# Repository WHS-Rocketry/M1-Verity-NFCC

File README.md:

## Current PCB validation

Open `NFCC.kicad_pro` in KiCad to load the project rules and bundled footprint library. The PCB includes the JLCPCB rule fixes and standard 2.54 mm GND / 5 V / PWM header spacing. See [change details](JLCPCB_FIXES.md).

Latest DRC: **0 violations, 0 unconnected items, 0 schematic parity issues**. Reports and a preview are in `checks/`. This is a prototype review design; a clean DRC does not establish production readiness. Power/load validation, final stackup and electrical/assembly review, and physical prototype testing remain necessary.

### Adjacent external connectors

The I²C and telemetry PicoBlade connectors are adjacent on the left edge, facing outward, with 12.2 mm between their centres. Their pin assignments are unchanged. The nearby battery-sense parts and I²C pullups were repositioned and the affected connections rerouted. The PWM headers retain 2.54 mm row spacing.

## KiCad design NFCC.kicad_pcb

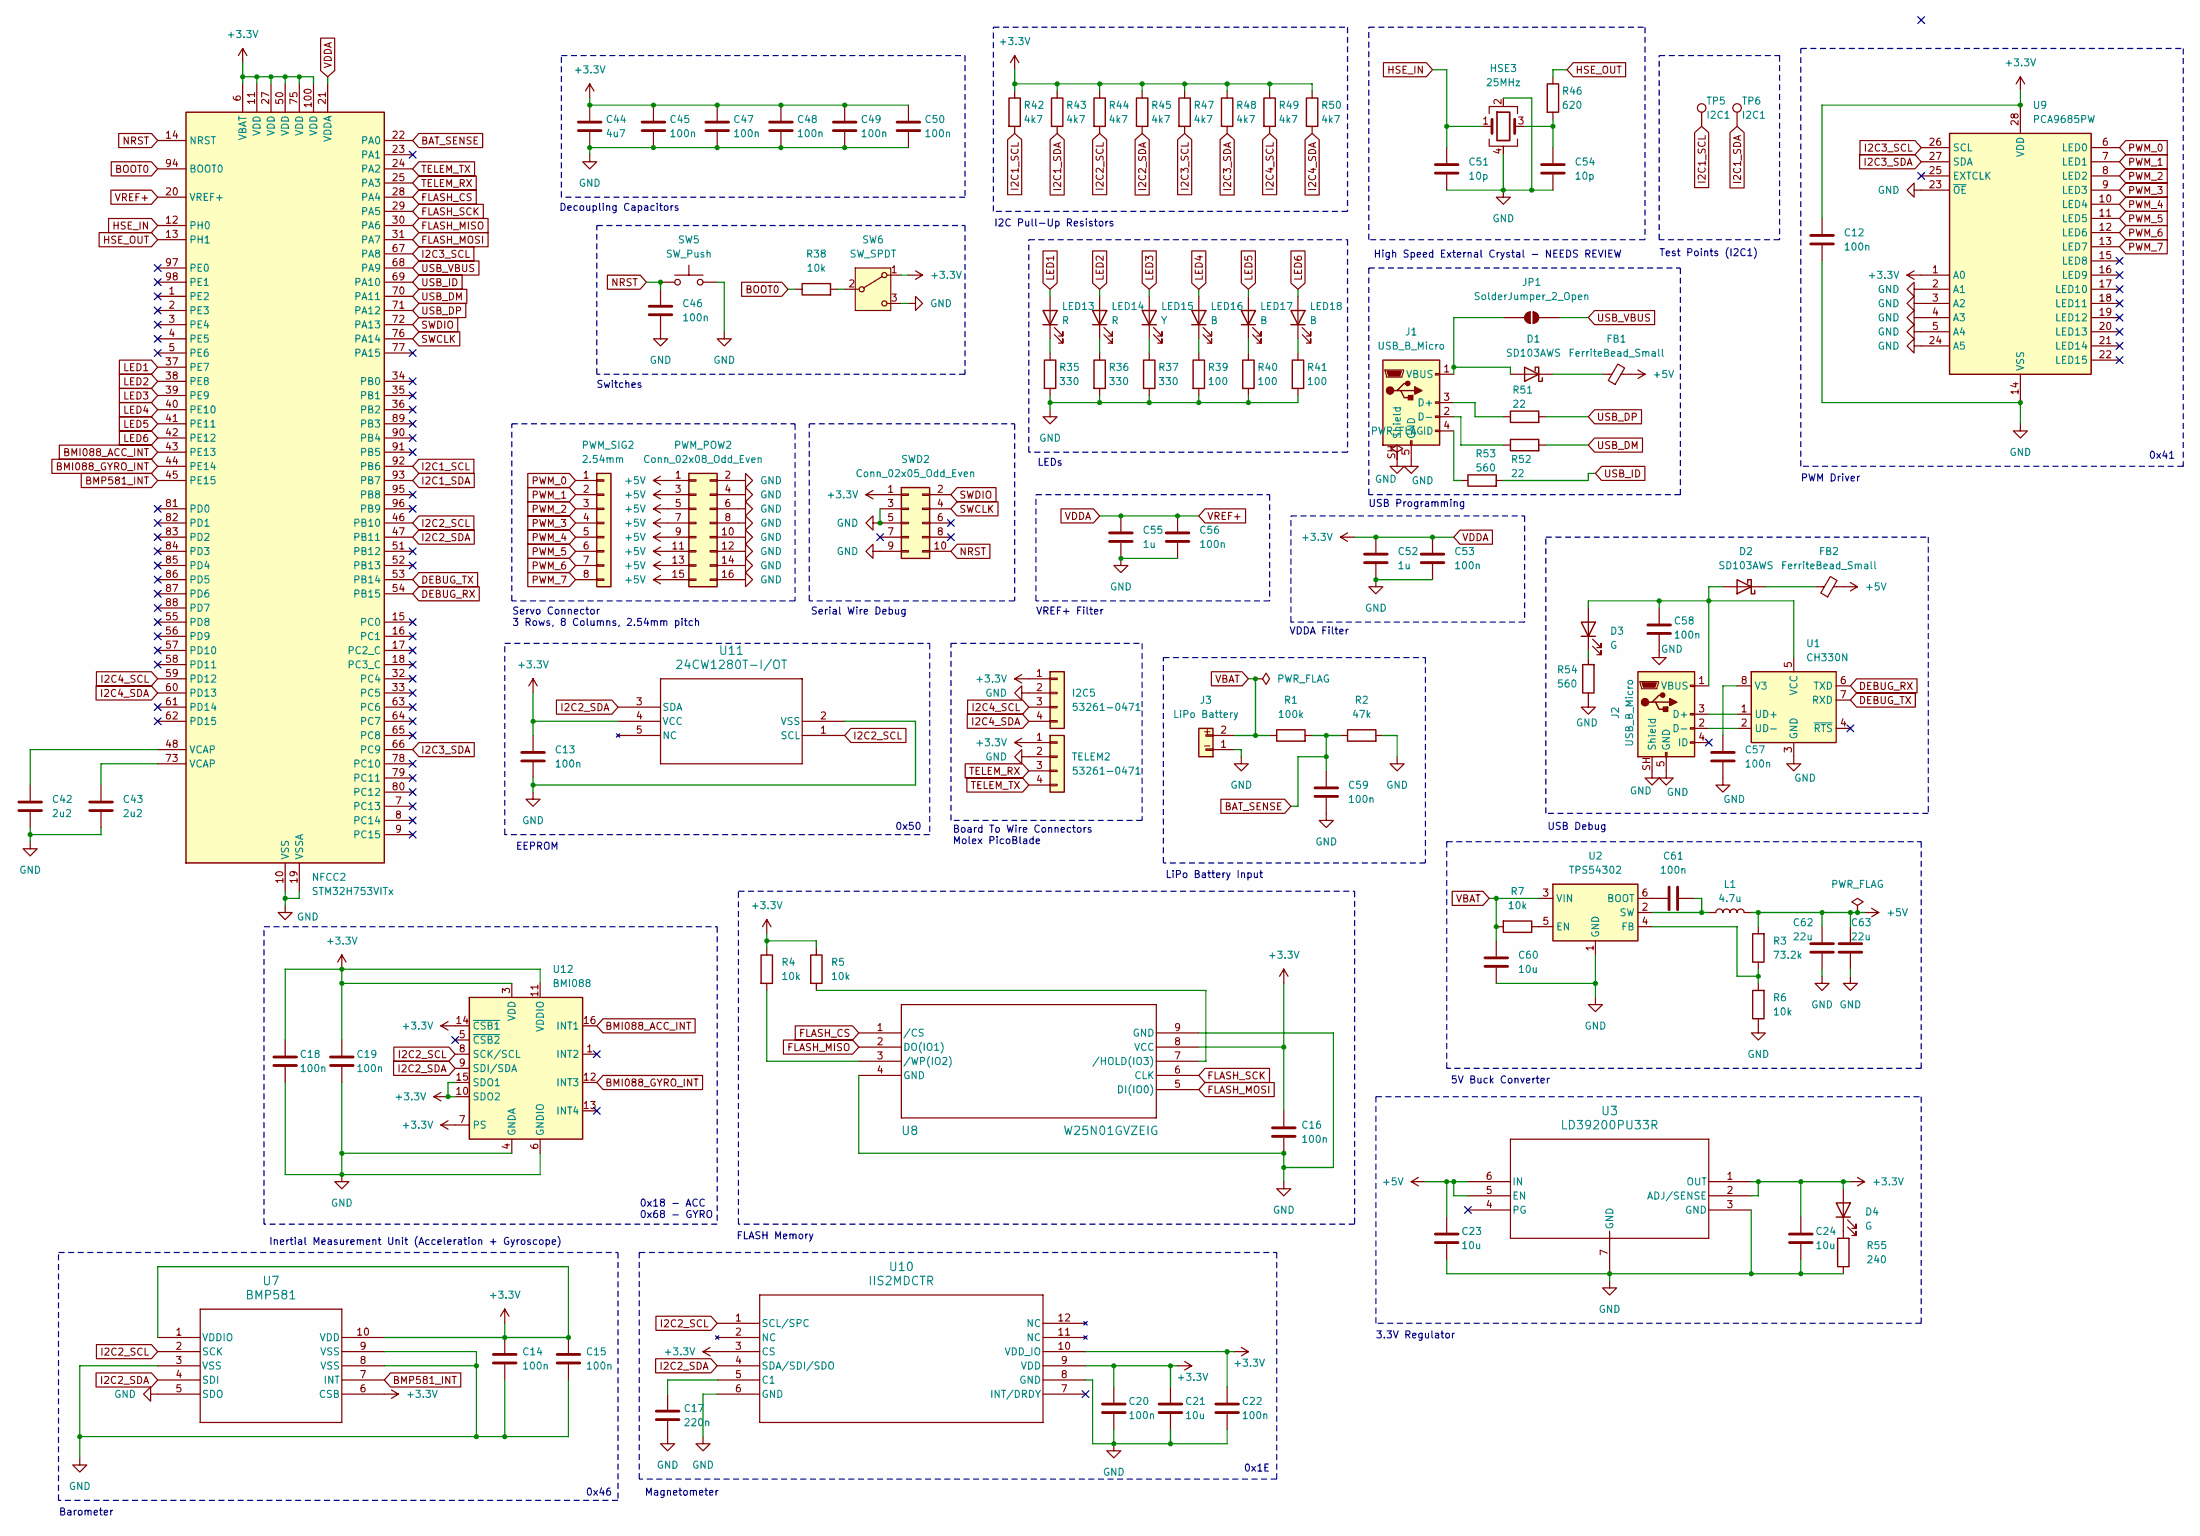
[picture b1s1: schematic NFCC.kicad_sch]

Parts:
C12: 100n; C_0603_1608Metric__C12
C13: 100n; C_0603_1608Metric__C13
C14: 100n; C_0603_1608Metric__C14
C15: 100n; C_0603_1608Metric__C15
C16: 100n; C_0603_1608Metric__C16
C17: 220n; C_0603_1608Metric__C17
C18: 100n; C_0603_1608Metric__C18
C19: 100n; C_0603_1608Metric__C19
C20: 100n; C_0603_1608Metric__C20
C21: 10u; C_0805_2012Metric__C21
C22: 100n; C_0603_1608Metric__C22
C23: 10u; C_0805_2012Metric__C23
C24: 10u; C_0805_2012Metric__C24
C42: 2u2; C_0603_1608Metric__C42
C43: 2u2; C_0603_1608Metric__C43
C44: 4u7; C_0603_1608Metric__C44
C45: 100n; C_0603_1608Metric__C45
C46: 100n; C_0603_1608Metric__C46
C47: 100n; C_0603_1608Metric__C47
C48: 100n; C_0603_1608Metric__C48
C49: 100n; C_0603_1608Metric__C49
C50: 100n; C_0603_1608Metric__C50
C51: 10p; C_0603_1608Metric__C51
C52: 1u; C_0603_1608Metric__C52
C53: 100n; C_0603_1608Metric__C53
C54: 10p; C_0603_1608Metric__C54
C55: 1u; C_0603_1608Metric__C55
C56: 100n; C_0603_1608Metric__C56
C57: 100n; C_0603_1608Metric__C57
C58: 100n; C_0603_1608Metric__C58
C59: 100n; C_0603_1608Metric__C59
C60: 10u; C_0805_2012Metric__C60
C61: 100n; C_0603_1608Metric__C61
C62: 22u; C_0805_2012Metric__C62
C63: 22u; C_0805_2012Metric__C63
D1: SD103AWS; D_SOD-323__D1
D2: SD103AWS; D_SOD-323__D2
D3: G; LED_0603_1608Metric__D3
D4: G; LED_0603_1608Metric__D4
FB1: FerriteBead_Small; L_0805_2012Metric__FB1
FB2: FerriteBead_Small; L_0805_2012Metric__FB2
HSE3: 25MHz; Crystal_SMD_3225-4Pin_3.2x2.5mm__HSE3
I2C5: 53261-0471; Molex_PicoBlade_53261-0471_1x04-1MP_P1.25mm_Horizontal__I2C5
J1: USB_B_Micro; USB_Micro-B_Molex_47346-0001__J1
J2: USB_B_Micro; USB_Micro-B_Molex_47346-0001__J2
J3: LiPo Battery; AMASS_XT60-M_1x02_P7.20mm_Vertical__J3
JP1: SolderJumper_2_Open; SolderJumper-2_P1.3mm_Open_RoundedPad1.0x1.5mm__JP1
L1: 4.7u; L_Bourns_SRN6045TA__L1
LED13: R; LED_0603_1608Metric__LED13
LED14: R; LED_0603_1608Metric__LED14
LED15: Y; LED_0603_1608Metric__LED15
LED16: B; LED_0603_1608Metric__LED16
LED17: B; LED_0603_1608Metric__LED17
LED18: B; LED_0603_1608Metric__LED18
NFCC2: STM32H753VITx; LQFP-100_14x14mm_P0.5mm__NFCC2
PWM_POW2: Conn_02x08_Odd_Even; PinHeader_2x08_P2.54mm_Vertical__PWM_POW2
PWM_SIG2: 2.54mm; PinHeader_1x08_P2.54mm_Vertical__PWM_SIG2
R1: 100k; R_0603_1608Metric__R1
R2: 47k; R_0603_1608Metric__R2
R3: 73.2k; R_0603_1608Metric__R3
R4: 10k; R_0603_1608Metric__R4
R5: 10k; R_0603_1608Metric__R5
R6: 10k; R_0603_1608Metric__R6
R7: 10k; R_0603_1608Metric__R7
R35: 330; R_0603_1608Metric__R35
R36: 330; R_0603_1608Metric__R36
R37: 330; R_0603_1608Metric__R37
R38: 10k; R_0603_1608Metric__R38
R39: 100; R_0603_1608Metric__R39
R40: 100; R_0603_1608Metric__R40
R41: 100; R_0603_1608Metric__R41
R42: 4k7; R_0603_1608Metric__R42
R43: 4k7; R_0603_1608Metric__R43
R44: 4k7; R_0603_1608Metric__R44
R45: 4k7; R_0603_1608Metric__R45
R46: 620; R_0603_1608Metric__R46
R47: 4k7; R_0603_1608Metric__R47
R48: 4k7; R_0603_1608Metric__R48
R49: 4k7; R_0603_1608Metric__R49
R50: 4k7; R_0603_1608Metric__R50
R51: 22; R_0603_1608Metric__R51
R52: 22; R_0603_1608Metric__R52
R53: 560; R_0603_1608Metric__R53
R54: 560; R_0603_1608Metric__R54
R55: 240; R_0603_1608Metric__R55
SW5: SW_Push; SW_SPST_SKQG_WithoutStem__SW5
SW6: SW_SPDT; SW_SPDT_PCM12__SW6
SWD2: Conn_02x05_Odd_Even; PinHeader_2x05_P1.27mm_Vertical__SWD2
TELEM2: 53261-0471; Molex_PicoBlade_53261-0471_1x04-1MP_P1.25mm_Horizontal__TEL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
TP5: I2C1; TestPoint_Pad_D1.5mm__TP5
TP6: I2C1; TestPoint_Pad_D1.5mm__TP6
U1: CH330N; SOIC-8_3.9x4.9mm_P1.27mm__U1
U2: TPS54302; SOT-23-6__U2
U3: LD39200PU33R; SON_DFN6_3X3_STM__U3
U7: BMP581; QFN10_BMP581_BOS__U7
U8: W25N01GVZEIG; WSON-8_8X6_WIN__U8
U9: PCA9685PW; TSSOP-28_4.4x9.7mm_P0.65mm__U9
U10: IIS2MDCTR; LGA-12_2X2X0P7_STM__U10
U11: 24CW1280T-I/OT; SOT-23-5_2P9X1P6_MCH__U11
U12: BMI088; Bosch_LGA-16_4.5x3mm_P0.5mm_LayoutBorder7x1y_ClockwisePinNu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

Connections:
+5V: C23.1, C62.1, C63.1, FB1.2, FB2.2, L1.2, PWM_POW2.1, PWM_POW2.3, PWM_POW2.5, PWM_POW2.7, PWM_POW2.9, PWM_POW2.11, PWM_POW2.13, PWM_POW2.15, R3.2, U3.5 (EN), U3.6 (IN)
BAT_SENSE: C59.1, NFCC2.22 (PA0), R1.2, R2.1
BMI088_ACC_INT: NFCC2.43 (PE13), U12.16 (INT1)
BMI088_GYRO_INT: NFCC2.44 (PE14), U12.12 (INT3)
BMP581_INT: NFCC2.45 (PE15), U7.7 (INT)
BOOT0: NFCC2.94 (BOOT0), R38.1
DEBUG_RX: NFCC2.54 (PB15), U1.6 (TXD)
DEBUG_TX: NFCC2.53 (PB14), U1.7 (RXD)
FLASH_CS: NFCC2.28 (PA4), U8.1 (/CS)
FLASH_MISO: NFCC2.30 (PA6), U8.2 (DO(IO1))
FLASH_MOSI: NFCC2.31 (PA7), U8.5 (DI(IO0))
FLASH_SCK: NFCC2.29 (PA5), U8.6 (CLK)
GND: C12.2, C13.2, C14.2, C15.2, C16.2, C17.2, C18.2, C19.2, C20.2, C21.2, C22.2, C23.2, C24.2, C42.2, C43.2, C44.2, C45.2, C46.2, C47.2, C48.2, C49.2, C50.2, C51.2, C52.2, C53.2, C54.2, C55.2, C56.2, C57.2, C58.2, C59.2, C60.2, C62.2, C63.2, HSE3.2, HSE3.4, I2C5.2, I2C5.MP (Mount_GND), J1.5 (GND), J1.SH (Shield), J2.5 (GND), J2.SH (Shield), J3.1, NFCC2.10 (VSS), NFCC2.19 (VSSA), NFCC2.26 (VSS), NFCC2.49 (VSS), NFCC2.74 (VSS), NFCC2.99 (VSS), PWM_POW2.2, PWM_POW2.4, PWM_POW2.6, PWM_POW2.8, PWM_POW2.10, PWM_POW2.12, PWM_POW2.14, PWM_POW2.16, R2.2, R6.1, R35.2, R36.2, R37.2, R39.2, R40.2, R41.2, R54.1, R55.1, SW5.2, SW6.3 (C), SWD2.3, SWD2.5, SWD2.9, TELEM2.2, TELEM2.MP (Mount_GND), U1.3 (GND), U2.1 (GND), U3.3 (GND), U3.7 (GND), U7.3 (VSS), U7.5 (SDO), U7.8 (VSS), U7.9 (VSS), U8.4 (GND), U8.9 (GND), U9.2 (A1), U9.3 (A2), U9.4 (A3), U9.5 (A4), U9.14 (VSS), U9.23 (~OE), U9.24 (A5), U10.6 (GND), U10.8 (GND), U11.2 (VSS), U12.2 (GNDA), U12.4 (GNDA), U12.6 (GNDIO)
HSE_IN: C51.1, HSE3.1, NFCC2.12 (PH0)
HSE_OUT: NFCC2.13 (PH1), R46.1
I2C1_SCL: NFCC2.92 (PB6), R42.2, TP5.1
I2C1_SDA: NFCC2.93 (PB7), R43.2, TP6.1
I2C2_SCL: NFCC2.46 (PB10), R44.2, U7.2 (SCK), U10.1 (SCL/SPC), U11.1 (SCL), U12.8 (SCK/SCL)
I2C2_SDA: NFCC2.47 (PB11), R45.2, U7.4 (SDI), U10.4 (SDA/SDI/SDO), U11.3 (SDA), U12.9 (SDI/SDA)
I2C3_SCL: NFCC2.67 (PA8), R47.2, U9.26 (SCL)
I2C3_SDA: NFCC2.66 (PC9), R48.2, U9.27 (SDA)
I2C4_SCL: I2C5.3, NFCC2.59 (PD12), R49.2
I2C4_SDA: I2C5.4, NFCC2.60 (PD13), R50.2
LED1: LED13.2 (A), NFCC2.37 (PE7)
LED2: LED14.2 (A), NFCC2.38 (PE8)
LED3: LED15.2 (A), NFCC2.39 (PE9)
LED4: LED16.2 (A), NFCC2.40 (PE10)
LED5: LED17.2 (A), NFCC2.41 (PE11)
LED6: LED18.2 (A), NFCC2.42 (PE12)
NRST: C46.1, NFCC2.14 (NRST), SW5.1, SWD2.10
unnamed: C42.1, NFCC2.48 (VCAP)
unnamed: C43.1, NFCC2.73 (VCAP)
unnamed: C54.1, HSE3.3, R46.2
unnamed: D1.2 (A), J1.1 (VBUS), JP1.1 (A)
unnamed: D1.1 (K), FB1.1
unnamed: C58.1, D2.2 (A), D3.2 (A), J2.1 (VBUS), U1.5 (VCC)
unnamed: D2.1 (K), FB2.1
unnamed: D3.1 (K), R54.2
unnamed: D4.1 (K), R55.2
unnamed: J1.3 (D+), R51.1
unnamed: J1.2 (D-), R52.1
unnamed: J1.4 (ID), R53.1
unnamed: J2.3 (D+), U1.1 (UD+)
unnamed: J2.2 (D-), U1.2 (UD-)
unnamed: LED13.1 (K), R35.1
unnamed: LED14.1 (K), R36.1
unnamed: LED15.1 (K), R37.1
unnamed: LED16.1 (K), R39.1
unnamed: LED17.1 (K), R40.1
unnamed: LED18.1 (K), R41.1
unnamed: R38.2, SW6.2 (B)
unnamed: C57.1, U1.8 (V3)
unnamed: C61.1, U2.6 (BOOT)
unnamed: R7.1, U2.5 (EN)
unnamed: R3.1, R6.2, U2.4 (FB)
unnamed: C61.2, L1.1, U2.2 (SW)
unnamed: R5.2, U8.7 (/HOLD(IO3))
unnamed: R4.2, U8.3 (/WP(IO2))
unnamed: C17.1, U10.5 (C1)
PWM_0: PWM_SIG2.1, U9.6 (LED0)
PWM_1: PWM_SIG2.2, U9.7 (LED1)
PWM_2: PWM_SIG2.3, U9.8 (LED2)
PWM_3: PWM_SIG2.4, U9.9 (LED3)
PWM_4: PWM_SIG2.5, U9.10 (LED4)
PWM_5: PWM_SIG2.6, U9.11 (LED5)
PWM_6: PWM_SIG2.7, U9.12 (LED6)
PWM_7: PWM_SIG2.8, U9.13 (LED7)
SWCLK: NFCC2.76 (PA14), SWD2.4
SWDIO: NFCC2.72 (PA13), SWD2.2
TELEM_RX: NFCC2.25 (PA3), TELEM2.3
TELEM_TX: NFCC2.24 (PA2), TELEM2.4
USB_DM: NFCC2.70 (PA11), R52.2
USB_DP: NFCC2.71 (PA12), R51.2
USB_ID: NFCC2.69 (PA10), R53.2
USB_VBUS: JP1.2 (B), NFCC2.68 (PA9)
VBAT: C60.1, J3.2, R1.1, R7.2, U2.3 (VIN)
VDDA: C12.1, C13.1, C14.1, C15.1, C16.1, C18.1, C19.1, C20.1, C21.1, C22.1, C24.1, C44.1, C45.1, C47.1, C48.1, C49.1, C50.1, C52.1, C53.1, C55.1, C56.1, D4.2 (A), I2C5.1, NFCC2.6 (VBAT), NFCC2.11 (VDD), NFCC2.20 (VREF+), NFCC2.21 (VDDA), NFCC2.27 (VDD), NFCC2.50 (VDD), NFCC2.75 (VDD), NFCC2.100 (VDD), R4.1, R5.1, R42.1, R43.1, R44.1, R45.1, R47.1, R48.1, R49.1, R50.1, SW6.1 (A), SWD2.1, TELEM2.1, U3.1 (OUT), U3.2 (ADJ/SENSE), U7.1 (VDDIO), U7.6 (CSB), U7.10 (VDD), U8.8 (VCC), U9.1 (A0), U9.28 (VDD), U10.3 (CS), U10.9 (VDD), U10.10 (VDD_IO), U11.4 (VCC), U12.3 (VDD), U12.7 (PS), U12.10 (SDO2), U12.11 (VDDIO), U12.14 (~CSB1), U12.15 (SDO1)

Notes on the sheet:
LiPo Battery Input
PWM Driver
Board To Wire Connectors Molex PicoBlade
LEDs
Servo Connector 3 Rows, 8 Columns, 2.54mm pitch
FLASH Memory
I2C Pull-Up Resistors
0x1E
VDDA Filter
Decoupling Capacitors
Switches
0x41
0x46
0x18 - ACC 0x68 - GYRO
VREF+ Filter
5V Buck Converter
Magnetometer
Test Points (I2C1)
3.3V Regulator
Serial Wire Debug
0x50
USB Debug
USB Programming
Barometer
Inertial Measurement Unit (Acceleration + Gyroscope)
High Speed External Crystal - NEEDS REVIEW
EEPROM

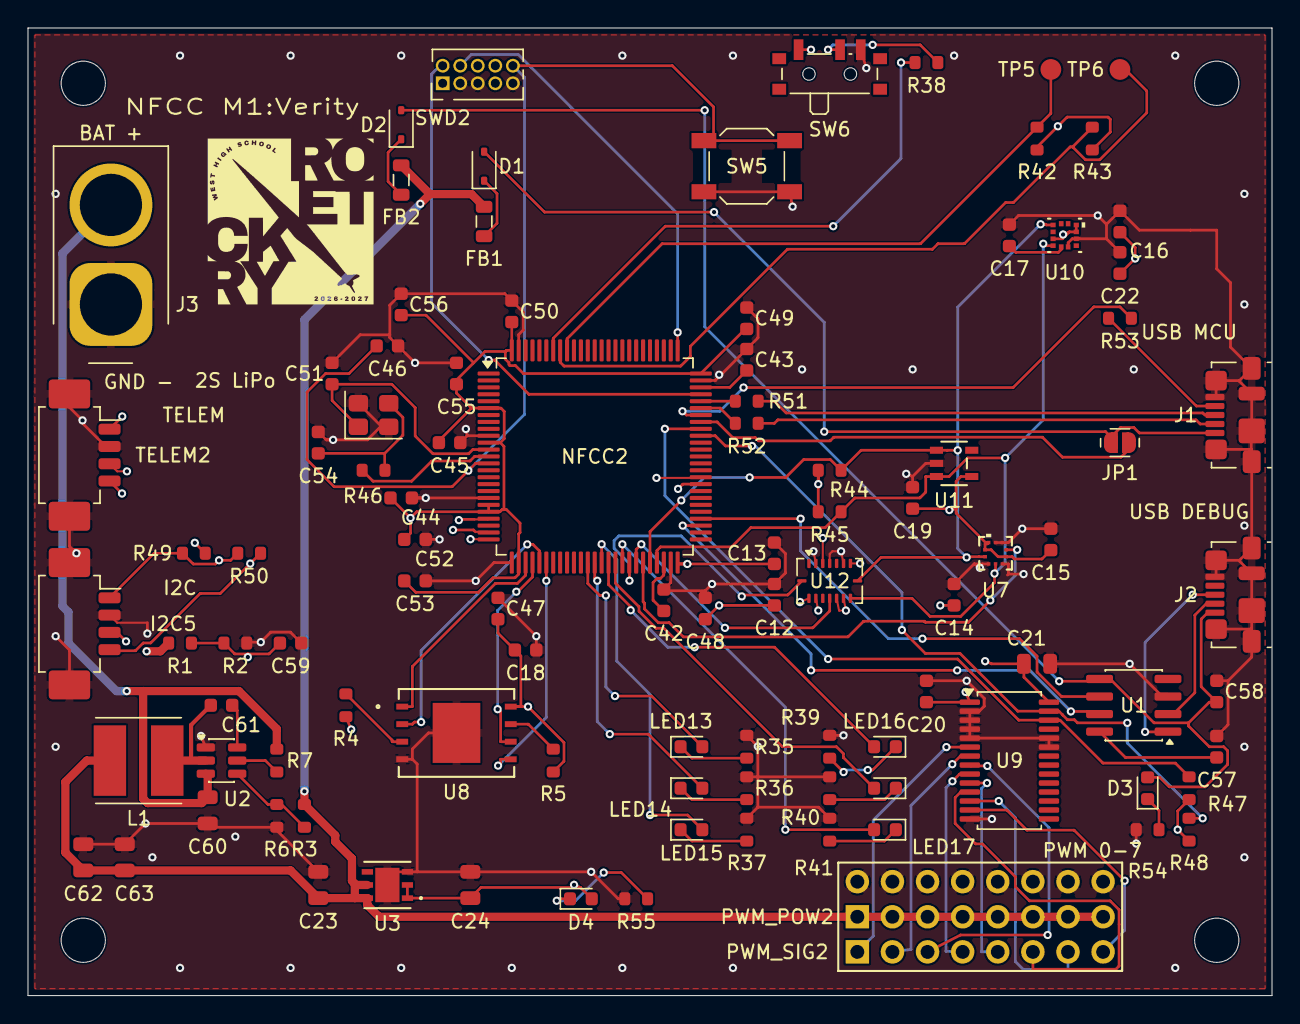
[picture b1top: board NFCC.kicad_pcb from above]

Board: 4 copper layers, 90.0 x 70.0 mm, 104 parts (0 on the bottom side), 77 nets.

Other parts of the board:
H1, H2, H3, H4: M3; MountingHole_3.2mm_M3

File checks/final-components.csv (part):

reference,value,footprint,x_mm,y_mm,rotation_deg
C12,100n,<pcbnew.LIB_ID; proxy of <Swig Object of type 'LIB_ID *' at 0x104eae8f0> >,114.0,101.0,90.0
C13,100n,<pcbnew.LIB_ID; proxy of <Swig Object of type 'LIB_ID *' at 0x10539ddf0> >,114.0,98.0,90.0
C14,100n,<pcbnew.LIB_ID; proxy of <Swig Object of type 'LIB_ID *' at 0x1053ae130> >,127.0,101.0,90.0
C15,100n,<pcbnew.LIB_ID; proxy of <Swig Object of type 'LIB_ID *' at 0x1052aca30> >,134.0,97.0,90.0
C16,100n,<pcbnew.LIB_ID; proxy of <Swig Object of type 'LIB_ID *' at 0x1052ac870> >,139.0,74.0,90.0
C17,220n,<pcbnew.LIB_ID; proxy of <Swig Object of type 'LIB_ID *' at 0x1052acd30> >,131.0,75.0,90.0
C18,100n,<pcbnew.LIB_ID; proxy of <Swig Object of type 'LIB_ID *' at 0x1052acc30> >,96.0,105.0,0.0
C19,100n,<pcbnew.LIB_ID; proxy of <Swig Object of type 'LIB_ID *' at 0x1052aca30> >,124.0,94.0,90.0
C20,100n,<pcbnew.LIB_ID; proxy of <Swig Object of type 'LIB_ID *' at 0x1052ac870> >,125.0,108.0,90.0
C21,10u,<pcbnew.LIB_ID; proxy of <Swig Object of type 'LIB_ID *' at 0x1052acd30> >,133.0,106.0,0.0
C22,100n,<pcbnew.LIB_ID; proxy of <Swig Object of type 'LIB_ID *' at 0x1052acc30> >,139.0,77.0,90.0
C23,10u,<pcbnew.LIB_ID; proxy of <Swig Object of type 'LIB_ID *' at 0x1052ac5b0> >,81.0,122.0,90.0
C24,10u,<pcbnew.LIB_ID; proxy of <Swig Object of type 'LIB_ID *' at 0x1052ac870> >,92.0,122.0,90.0
C42,2u2,<pcbnew.LIB_ID; proxy of <Swig Object of type 'LIB_ID *' at 0x1052acd30> >,106.0,101.4,90.0
C43,2u2,<pcbnew.LIB_ID; proxy of <Swig Object of type 'LIB_ID *' at 0x1052acc30> >,112.0,84.0,90.0
C44,4u7,<pcbnew.LIB_ID; proxy of <Swig Object of type 'LIB_ID *' at 0x1052ac5b0> >,87.0,94.0,0.0
C45,100n,<pcbnew.LIB_ID; proxy of <Swig Object of type 'LIB_ID *' at 0x1052ac870> >,90.5,90.0,0.0
C46,100n,<pcbnew.LIB_ID; proxy of <Swig Object of type 'LIB_ID *' at 0x1052acd30> >,86.0,83.0,0.0
C47,100n,<pcbnew.LIB_ID; proxy of <Swig Object of type 'LIB_ID *' at 0x1052acc30> >,94.0,102.0,90.0
C48,100n,<pcbnew.LIB_ID; proxy of <Swig Object of type 'LIB_ID *' at 0x1052ac5b0> >,109.0,102.0,90.0
C49,100n,<pcbnew.LIB_ID; proxy of <Swig Object of type 'LIB_ID *' at 0x1052ac870> >,112.0,81.0,90.0
C50,100n,<pcbnew.LIB_ID; proxy of <Swig Object of type 'LIB_ID *' at 0x1052acd30> >,95.0,80.5,90.0
C51,10p,<pcbnew.LIB_ID; proxy of <Swig Object of type 'LIB_ID *' at 0x1052acc30> >,82.0,85.0,90.0
C52,1u,<pcbnew.LIB_ID; proxy of <Swig Object of type 'LIB_ID *' at 0x1052ac5b0> >,88.0,97.0,0.0
C53,100n,<pcbnew.LIB_ID; proxy of <Swig Object of type 'LIB_ID *' at 0x1052ac870> >,88.0,100.0,0.0
C54,10p,<pcbnew.LIB_ID; proxy of <Swig Object of type 'LIB_ID *' at 0x1052acd30> >,81.0,90.0,90.0
C55,1u,<pcbnew.LIB_ID; proxy of <Swig Object of type 'LIB_ID *' at 0x1052acc30> >,91.0,85.0,90.0
C56,100n,<pcbnew.LIB_ID; proxy of <Swig Object of type 'LIB_ID *' at 0x1052ac5b0> >,87.0,80.0,90.0
C57,100n,<pcbnew.LIB_ID; proxy of <Swig Object of type 'LIB_ID *' at 0x1052ac870> >,146.0,112.0,90.0
C58,100n,<pcbnew.LIB_ID; proxy of <Swig Object of type 'LIB_ID *' at 0x1052acd30> >,146.0,108.0,90.0
C59,100n,<pcbnew.LIB_ID; proxy of <Swig Object of type 'LIB_ID *' at 0x1052acc30> >,71.0,103.0,0.0
C60,10u,<pcbnew.LIB_ID; proxy of <Swig Object of type 'LIB_ID *' at 0x1052ac5b0> >,73.0,116.6,-90.0
C61,100n,<pcbnew.LIB_ID; proxy of <Swig Object of type 'LIB_ID *' at 0x1052ac870> >,74.0,109.0,180.0
C62,22u,<pcbnew.LIB_ID; proxy of <Swig Object of type 'LIB_ID *' at 0x1052acd30> >,64.0,120.0,90.0
C63,22u,<pcbnew.LIB_ID; proxy of <Swig Object of type 'LIB_ID *' at 0x1052acc30> >,67.0,120.0,90.0
D1,SD103AWS,<pcbnew.LIB_ID; proxy of <Swig Object of type 'LIB_ID *' at 0x1052ac5b0> >,93.0,70.0,90.0
D2,SD103AWS,<pcbnew.LIB_ID; proxy of <Swig Object of type 'LIB_ID *' at 0x1052ac870> >,87.0,67.0,90.0
D3,G,<pcbnew.LIB_ID; proxy of <Swig Object of type 'LIB_ID *' at 0x1052acd30> >,141.0,115.0,90.0
D4,G,<pcbnew.LIB_ID; proxy of <Swig Object of type 'LIB_ID *' at 0x1052acc30> >,100.0,123.0,0.0
FB1,FerriteBead_Small,<pcbnew.LIB_ID; proxy of <Swig Object of type 'LIB_ID *' at 0x1052ac5b0> >,93.0,74.0,90.0
FB2,FerriteBead_Small,<pcbnew.LIB_ID; proxy of <Swig Object of type 'LIB_ID *' at 0x1052ac270> >,87.0,71.0,90.0
G***,LOGO,<pcbnew.LIB_ID; proxy of <Swig Object of type 'LIB_ID *' at 0x1052acd30> >,79.0,74.0,0.0
H1,M3,<pcbnew.LIB_ID; proxy of <Swig Object of type 'LIB_ID *' at 0x1052acc30> >,64.0,64.0,0.0
H2,M3,<pcbnew.LIB_ID; proxy of <Swig Object of type 'LIB_ID *' at 0x1052ac5b0> >,146.0,64.0,0.0
H3,M3,<pcbnew.LIB_ID; proxy of <Swig Object of type 'LIB_ID *' at 0x1052aceb0> >,146.0,126.0,0.0
H4,M3,<pcbnew.LIB_ID; proxy of <Swig Object of type 'LIB_ID *' at 0x1052acd30> >,64.0,126.0,0.0
HSE3,25MHz,<pcbnew.LIB_ID; proxy of <Swig Object of type 'LIB_ID *' at 0x1052acc30> >,85.0,88.0,0.0
I2C5,53261-0471,<pcbnew.LIB_ID; proxy of <Swig Object of type 'LIB_ID *' at 0x1052ac5b0> >,146.5,74.0,90.0
J1,USB_B_Micro,<pcbnew.LIB_ID; proxy of <Swig Object of type 'LIB_ID *' at 0x1052aceb0> >,147.33,88.0,90.0
J2,USB_B_Micro,<pcbnew.LIB_ID; proxy of <Swig Object of type 'LIB_ID *' at 0x1052acd30> >,147.33,101.0,90.0
J3,LiPo Battery,<pcbnew.LIB_ID; proxy of <Swig Object of type 'LIB_ID *' at 0x1052acc30> >,66.0,80.0,90.0
JP1,SolderJumper_2_Open,<pcbnew.LIB_ID; proxy of <Swig Object of type 'LIB_ID *' at 0x1052ac5b0> >,139.0,90.0,0.0
L1,4.7u,<pcbnew.LIB_ID; proxy of <Swig Object of type 'LIB_ID *' at 0x1052aceb0> >,68.0,113.0,180.0
LED13,R,<pcbnew.LIB_ID; proxy of <Swig Object of type 'LIB_ID *' at 0x1052acd30> >,108.0,112.0,0.0
LED14,R,<pcbnew.LIB_ID; proxy of <Swig Object of type 'LIB_ID *' at 0x1052acef0> >,108.0,115.0,0.0
LED15,Y,<pcbnew.LIB_ID; proxy of <Swig Object of type 'LIB_ID *' at 0x1052ac430> >,108.0,118.0,0.0
LED16,B,<pcbnew.LIB_ID; proxy of <Swig Object of type 'LIB_ID *' at 0x1052acc30> >,122.0,112.0,180.0
LED17,B,<pcbnew.LIB_ID; proxy of <Swig Object of type 'LIB_ID *' at 0x1052acd30> >,122.0,115.0,180.0
LED18,B,<pcbnew.LIB_ID; proxy of <Swig Object of type 'LIB_ID *' at 0x1052acef0> >,122.0,118.0,180.0
NFCC2,STM32H753VITx,<pcbnew.LIB_ID; proxy of <Swig Object of type 'LIB_ID *' at 0x1052acd30> >,101.0,91.0,0.0
PWM_POW2,Conn_02x08_Odd_Even,<pcbnew.LIB_ID; proxy of <Swig Object of type 'LIB_ID *' at 0x1052acef0> >,120.0,124.3,90.0
PWM_SIG2,2.54mm,<pcbnew.LIB_ID; proxy of <Swig Object of type 'LIB_ID *' at 0x1052de0f0> >,120.0,128.0,90.0
R1,100k,<pcbnew.LIB_ID; proxy of <Swig Object of type 'LIB_ID *' at 0x1052acef0> >,63.0,103.0,0.0
R2,47k,<pcbnew.LIB_ID; proxy of <Swig Object of type 'LIB_ID *' at 0x1052de0b0> >,67.0,103.0,0.0
R3,73.2k,<pcbnew.LIB_ID; proxy of <Swig Object of type 'LIB_ID *' at 0x1052de130> >,80.0,117.0,90.0
R35,330,<pcbnew.LIB_ID; proxy of <Swig Object of type 'LIB_ID *' at 0x1052de0f0> >,112.0,112.0,90.0
R36,330,<pcbnew.LIB_ID; proxy of <Swig Object of type 'LIB_ID *' at 0x1052de030> >,112.0,115.0,90.0
R37,330,<pcbnew.LIB_ID; proxy of <Swig Object of type 'LIB_ID *' at 0x1052de0b0> >,112.0,118.0,90.0
R38,10k,<pcbnew.LIB_ID; proxy of <Swig Object of type 'LIB_ID *' at 0x1052de130> >,125.0,62.5,0.0
R39,100,<pcbnew.LIB_ID; proxy of <Swig Object of type 'LIB_ID *' at 0x1052de0f0> >,118.0,112.0,90.0
R4,10k,<pcbnew.LIB_ID; proxy of <Swig Object of type 'LIB_ID *' at 0x1052de030> >,83.0,109.0,90.0
R40,100,<pcbnew.LIB_ID; proxy of <Swig Object of type 'LIB_ID *' at 0x1052de0b0> >,118.0,115.0,90.0
R41,100,<pcbnew.LIB_ID; proxy of <Swig Object of type 'LIB_ID *' at 0x1052de130> >,118.0,118.0,90.0
R42,4k7,<pcbnew.LIB_ID; proxy of <Swig Object of type 'LIB_ID *' at 0x1052de0f0> >,133.0,68.0,90.0
R43,4k7,<pcbnew.LIB_ID; proxy of <Swig Object of type 'LIB_ID *' at 0x1052de030> >,137.0,68.0,90.0
R44,4k7,<pcbnew.LIB_ID; proxy of <Swig Object of type 'LIB_ID *' at 0x1052de0b0> >,118.0,92.0,0.0
R45,4k7,<pcbnew.LIB_ID; proxy of <Swig Object of type 'LIB_ID *' at 0x1052de130> >,118.0,95.0,0.0
R46,620,<pcbnew.LIB_ID; proxy of <Swig Object of type 'LIB_ID *' at 0x1052de0f0> >,85.0,92.0,0.0
R47,4k7,<pcbnew.LIB_ID; proxy of <Swig Object of type 'LIB_ID *' at 0x1052de030> >,144.0,115.0,90.0
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
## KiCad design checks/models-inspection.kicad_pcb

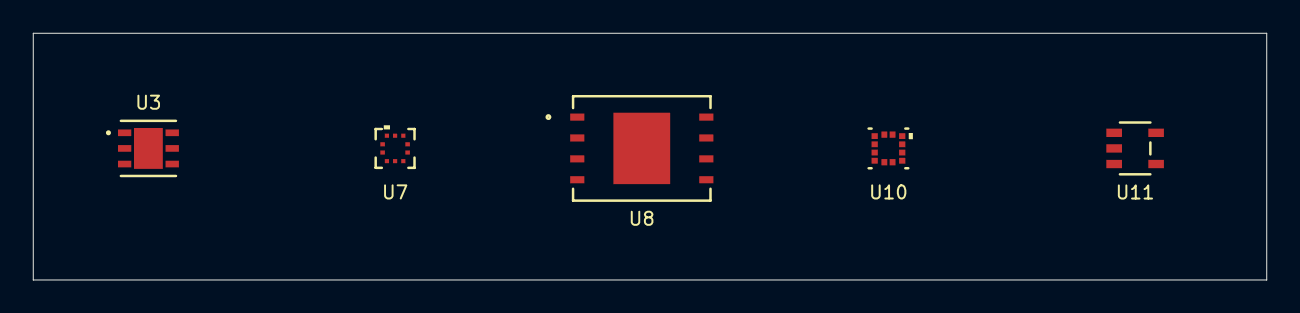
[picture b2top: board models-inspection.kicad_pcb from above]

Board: 2 copper layers, 75.0 x 15.0 mm, 5 parts (0 on the bottom side), 5 nets, no tracks yet.

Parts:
U3: LD39200PU33R; SON_DFN6_3X3_STM__U3
U7: BMP581; QFN10_BMP581_BOS__U7
U8: W25N01GVZEIG; WSON-8_8X6_WIN__U8
U10: IIS2MDCTR; LGA-12_2X2X0P7_STM__U10
U11: 24CW1280T-I/OT; SOT-23-5_2P9X1P6_MCH__U11

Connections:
+5V: U3.5, U3.6
GND: U3.3, U3.7, U7.3, U7.5, U7.8, U7.9, U8.4, U8.9, U10.6, U10.8, U11.2
I2C2_SCL: U7.2, U10.1, U11.1
I2C2_SDA: U7.4, U10.4, U11.3
VDDA: U3.1, U3.2, U7.1, U7.6, U7.10, U8.8, U10.3, U10.9, U10.10, U11.4
